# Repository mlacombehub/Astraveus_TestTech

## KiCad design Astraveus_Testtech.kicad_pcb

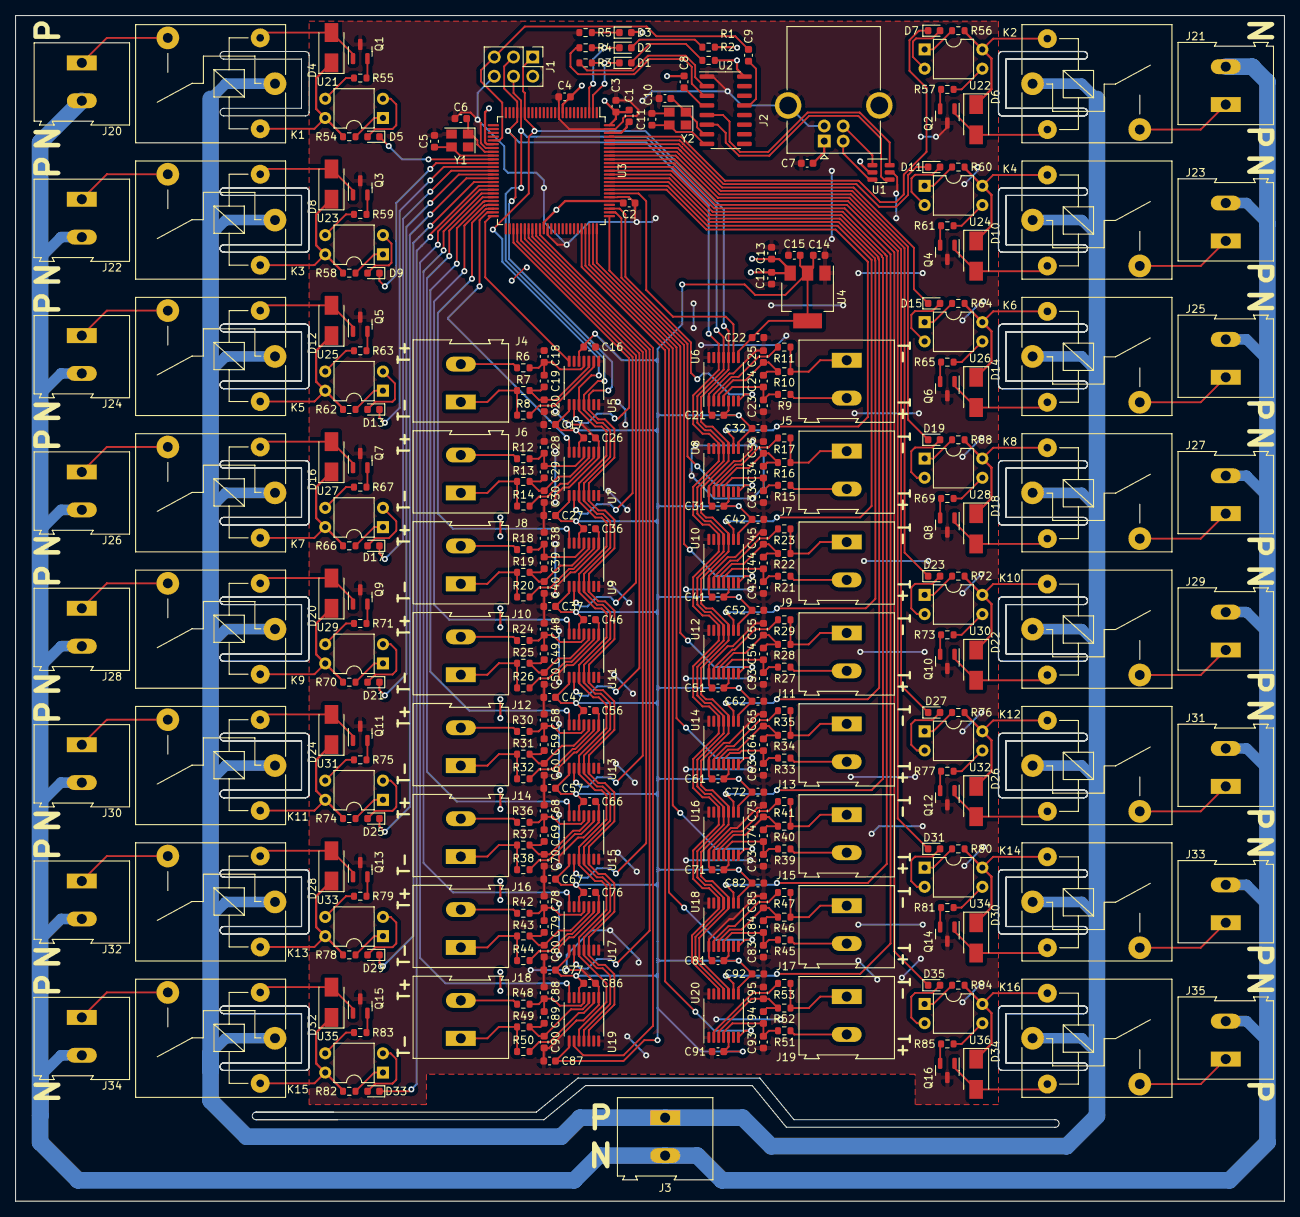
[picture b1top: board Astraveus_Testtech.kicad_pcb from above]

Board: 2 copper layers, 167.5 x 156.5 mm, 320 parts (0 on the bottom side), 251 nets.

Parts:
C1, C3, C4, C7, C8, C9, C16, C17, C19, C21, C22, C24, C26, C27, C29, C31, C32, C34, C36, C37, C39, C41, C42, C44, C46, C47, C49, C51, C52, C54, C56, C57, C59, C61, C62, C64, C66, C67, C69, C71, C72, C74, C76, C77, C79, C81, C82, C84, C86, C87, C89, C91, C92, C94: 100nF; C_0603_1608Metric
C2: 10uF; C_0603_1608Metric
C5, C6, C10, C11: 22pF; C_0603_1608Metric
C12, C15: 4.7uF; C_0603_1608Metric
C13, C14: 1uF; C_0603_1608Metric
C18, C20, C23, C25, C28, C30, C33, C35, C38, C40, C43, C45, C48, C50, C53, C55, C58, C60, C63, C65, C68, C70, C73, C75, C78, C80, C83, C85, C88, C90, C93, C95: 10nF; C_0603_1608Metric
D1, D2, D3, D5, D7, D9, D11, D13, D15, D17, D19, D21, D23, D25, D27, D29, D31, D33, D35: LED_Small; D_0603_1608Metric
D4, D6, D8, D10, D12, D14, D16, D18, D20, D22, D24, D26, D28, D30, D32, D34: 1N4007; D_SMA
J1: AVR-ISP-6; PinHeader_2x03_P2.54mm_Vertical
J2: USB_B; USB_B_OST_USB-B1HSxx_Horizontal
J3, J4, J5, J6, J7, J8, J9, J10, J11, J12, J13, J14, J15, J16, J17, J18, J19, J20, J21, J22, J23, J24, J25, J26, J27, J28, J29, J30, J31, J32, J33, J34, J35: Screw_Terminal_01x02; TerminalBlock_Altech_AK300-2_P5.00mm
K1, K2, K3, K4, K5, K6, K7, K8, K9, K10, K11, K12, K13, K14, K15, K16: SANYOU_SRD_Form_C; Relay_SPST_SANYOU_SRD_Series_Form_A
Q1, Q2, Q3, Q4, Q5, Q6, Q7, Q8, Q9, Q10, Q11, Q12, Q13, Q14, Q15, Q16: BC547; SOT-23
R1, R3: 10K; R_0603_1608Metric
R2, R4, R5: 1K; R_0603_1608Metric
R6, R7, R8, R9, R10, R11, R12, R13, R14, R15, R16, R17, R18, R19, R20, R21, R22, R23, R24, R25, R26, R27, R28, R29, R30, R31, R32, R33, R34, R35, R36, R37, R38, R39, R40, R41, R42, R43, R44, R45, R46, R47, R48, R49, R50, R51, R52, R53, R54, R55, R56, R57, R58, R59, R60, R61, R62, R63, R64, R65, R66, R67, R68, R69, R70, R71, R72, R73, R74, R75, R76, R77, R78, R79, R80, R81, R82, R83, R84, R85: 100; R_0603_1608Metric
U1: USBLC6-2SC6; SOT-23-6
U2: CH340G; SOIC-16_3.9x9.9mm_P1.27mm
U3: ATmega2560-16A; TQFP-100_14x14mm_P0.5mm
U4: AMS1117-3.3; SOT-223-3_TabPin2
U5, U6, U7, U8, U9, U10, U11, U12, U13, U14, U15, U16, U17, U18, U19, U20: MAX31856; TSSOP-14_4.4x5mm_P0.65mm
U21, U22, U23, U24, U25, U26, U27, U28, U29, U30, U31, U32, U33, U34, U35, U36: PC817; DIP-4_W7.62mm
Y1: 16MHz; Crystal_SMD_3225-4Pin_3.2x2.5mm
Y2: 12MHz; Crystal_SMD_3225-4Pin_3.2x2.5mm

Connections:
+3.3V: C14.1, C15.1, C16.2, C17.2, C21.2, C22.2, C26.2, C27.2, C31.2, C32.2, C36.2, C37.2, C41.2, C42.2, C46.2, C47.2, C51.2, C52.2, C56.2, C57.2, C61.2, C62.2, C66.2, C67.2, C71.2, C72.2, C76.2, C77.2, C81.2, C82.2, C86.2, C87.2, C91.2, C92.2, U4.2 (VO), U5.5 (AVDD), U5.8 (DVDD), U6.5 (AVDD), U6.8 (DVDD), U7.5 (AVDD), U7.8 (DVDD), U8.5 (AVDD), U8.8 (DVDD), U9.5 (AVDD), U9.8 (DVDD), U10.5 (AVDD), U10.8 (DVDD), U11.5 (AVDD), U11.8 (DVDD), U12.5 (AVDD), U12.8 (DVDD), U13.5 (AVDD), U13.8 (DVDD), U14.5 (AVDD), U14.8 (DVDD), U15.5 (AVDD), U15.8 (DVDD), U16.5 (AVDD), U16.8 (DVDD), U17.5 (AVDD), U17.8 (DVDD), U18.5 (AVDD), U18.8 (DVDD), U19.5 (AVDD), U19.8 (DVDD), U20.5 (AVDD), U20.8 (DVDD)
+5V: C1.1, C2.1, C3.1, C4.1, C7.1, C8.2, C12.1, C13.1, D3.2 (A), D4.1 (K), D6.1 (K), D8.1 (K), D10.1 (K), D12.1 (K), D14.1 (K), D16.1 (K), D18.1 (K), D20.1 (K), D22.1 (K), D24.1 (K), D26.1 (K), D28.1 (K), D30.1 (K), D32.1 (K), D34.1 (K), J1.2 (VCC), J2.1 (VBUS), K1.5, K2.5, K3.5, K4.5, K5.5, K6.5, K7.5, K8.5, K9.5, K10.5, K11.5, K12.5, K13.5, K14.5, K15.5, K16.5, R1.2, R2.2, R54.2, R56.2, R58.2, R60.2, R62.2, R64.2, R66.2, R68.2, R70.2, R72.2, R74.2, R76.2, R78.2, R80.2, R82.2, R84.2, U1.2 (GND), U2.16 (VCC), U3.10 (VCC), U3.31 (VCC), U3.61 (VCC), U3.80 (VCC), U3.100 (AVCC), U4.3 (VI), U21.4, U22.4, U23.4, U24.4, U25.4, U26.4, U27.4, U28.4, U29.4, U30.4, U31.4, U32.4, U33.4, U34.4, U35.4, U36.4
/AREF: C1.2, U3.98 (AREF)
/CH0: D5.1 (K), U3.35 (PL0)
/CH1: D7.1 (K), U3.97 (PF0)
/CH2: D9.1 (K), U3.36 (PL1)
/CH3: D11.1 (K), U3.96 (PF1)
/CH4: D13.1 (K), U3.37 (PL2)
/CH5: D15.1 (K), U3.95 (PF2)
/CH6: D17.1 (K), U3.38 (PL3)
/CH7: D19.1 (K), U3.94 (PF3)
/CH8: D21.1 (K), U3.39 (PL4)
/CH9: D23.1 (K), U3.93 (PF4)
/CH10: D25.1 (K), U3.40 (PL5)
/CH11: D27.1 (K), U3.92 (PF5)
/CH12: D29.1 (K), U3.41 (PL6)
/CH13: D31.1 (K), U3.91 (PF6)
/CH14: D33.1 (K), U3.42 (PL7)
/CH15: D35.1 (K), U3.90 (PF7)
/RESET: C9.2, J1.5 (~RST), U3.30 (~RESET)
/RX: D1.1 (K), R3.2, U3.2 (PE0)
/SPI0: J1.1 (MISO), U3.20 (PB1), U5.10 (SCK), U6.10 (SCK), U7.10 (SCK), U8.10 (SCK), U9.10 (SCK), U10.10 (SCK), U11.10 (SCK), U12.10 (SCK), U13.10 (SCK), U14.10 (SCK), U15.10 (SCK), U16.10 (SCK), U17.10 (SCK), U18.10 (SCK), U19.10 (SCK), U20.10 (SCK)
/SPI1: J1.4 (MOSI), U3.21 (PB2), U5.11 (SDO), U6.11 (SDO), U7.11 (SDO), U8.11 (SDO), U9.11 (SDO), U10.11 (SDO), U11.11 (SDO), U12.11 (SDO), U13.11 (SDO), U14.11 (SDO), U15.11 (SDO), U16.11 (SDO), U17.11 (SDO), U18.11 (SDO), U19.11 (SDO), U20.11 (SDO)
/SPI2: J1.3 (SCK), U3.22 (PB3), U5.12 (SDI), U6.12 (SDI), U7.12 (SDI), U8.12 (SDI), U9.12 (SDI), U10.12 (SDI), U11.12 (SDI), U12.12 (SDI), U13.12 (SDI), U14.12 (SDI), U15.12 (SDI), U16.12 (SDI), U17.12 (SDI), U18.12 (SDI), U19.12 (SDI), U20.12 (SDI)
/TX: D2.1 (K), R4.2, U3.3 (PE1)
/~CS0: U3.53 (PC0), U5.9 (~CS)
/~CS1: U3.82 (PK7), U6.9 (~CS)
/~CS2: U3.54 (PC1), U7.9 (~CS)
/~CS3: U3.83 (PK6), U8.9 (~CS)
/~CS4: U3.55 (PC2), U9.9 (~CS)
/~CS5: U3.84 (PK5), U10.9 (~CS)
/~CS6: U3.56 (PC3), U11.9 (~CS)
/~CS7: U3.85 (PK4), U12.9 (~CS)
/~CS8: U3.57 (PC4), U13.9 (~CS)
/~CS9: U3.86 (PK3), U14.9 (~CS)
/~CS10: U3.58 (PC5), U15.9 (~CS)
/~CS11: U3.87 (PK2), U16.9 (~CS)
/~CS12: U3.59 (PC6), U17.9 (~CS)
/~CS13: U3.88 (PK1), U18.9 (~CS)
/~CS14: U3.60 (PC7), U19.9 (~CS)
/~CS15: U3.89 (PK0), U20.9 (~CS)
/~DRDY0: U3.50 (PD7), U5.7 (~DRDY)
/~DRDY1: U3.78 (PA0), U6.7 (~DRDY)
/~DRDY2: U3.49 (PD6), U7.7 (~DRDY)
/~DRDY3: U3.77 (PA1), U8.7 (~DRDY)
/~DRDY4: U3.48 (PD5), U9.7 (~DRDY)
/~DRDY5: U3.76 (PA2), U10.7 (~DRDY)
/~DRDY6: U3.47 (PD4), U11.7 (~DRDY)
/~DRDY7: U3.75 (PA3), U12.7 (~DRDY)
/~DRDY8: U3.46 (PD3), U13.7 (~DRDY)
/~DRDY9: U3.74 (PA4), U14.7 (~DRDY)
/~DRDY10: U3.45 (PD2), U15.7 (~DRDY)
/~DRDY11: U3.73 (PA5), U16.7 (~DRDY)
/~DRDY12: U3.44 (PD1), U17.7 (~DRDY)
/~DRDY13: U3.72 (PA6), U18.7 (~DRDY)
/~DRDY14: U3.43 (PD0), U19.7 (~DRDY)
/~DRDY15: U3.71 (PA7), U20.7 (~DRDY)
GND: C2.2, C3.2, C4.2, C5.2, C6.2, C7.2, C10.2, C11.2, C12.2, C13.2, C14.2, C15.2, C16.1, C17.1, C18.1, C20.2, C21.1, C22.1, C23.1, C25.2, C26.1, C27.1, C28.1, C30.2, C31.1, C32.1, C33.1, C35.2, C36.1, C37.1, C38.1, C40.2, C41.1, C42.1, C43.1, C45.2, C46.1, C47.1, C48.1, C50.2, C51.1, C52.1, C53.1, C55.2, C56.1, C57.1, C58.1, C60.2, C61.1, C62.1, C63.1, C65.2, C66.1, C67.1, C68.1, C70.2, C71.1, C72.1, C73.1, C75.2, C76.1, C77.1, C78.1, C80.2, C81.1, C82.1, C83.1, C85.2, C86.1, C87.1, C88.1, C90.2, C91.1, C92.1, C93.1, C95.2, J1.6 (GND), J2.4 (GND), J2.5 (Shield), Q1.3 (E), Q2.3 (E), Q3.3 (E), Q4.3 (E), Q5.3 (E), Q6.3 (E), Q7.3 (E), Q8.3 (E), Q9.3 (E), Q10.3 (E), Q11.3 (E), Q12.3 (E), Q13.3 (E), Q14.3 (E), Q15.3 (E), Q16.3 (E), R5.1, U1.5 (VBUS), U2.1 (GND), U3.11 (GND), U3.32 (GND), U3.62 (GND), U3.81 (GND), U3.99 (GND), U4.1 (GND), U5.1 (AGND), U5.14 (DGND), U6.1 (AGND), U6.14 (DGND), U7.1 (AGND), U7.14 (DGND), U8.1 (AGND), U8.14 (DGND), U9.1 (AGND), U9.14 (DGND), U10.1 (AGND), U10.14 (DGND), U11.1 (AGND), U11.14 (DGND), U12.1 (AGND), U12.14 (DGND), U13.1 (AGND), U13.14 (DGND), U14.1 (AGND), U14.14 (DGND), U15.1 (AGND), U15.14 (DGND), U16.1 (AGND), U16.14 (DGND), U17.1 (AGND), U17.14 (DGND), U18.1 (AGND), U18.14 (DGND), U19.1 (AGND), U19.14 (DGND), U20.1 (AGND), U20.14 (DGND), Y1.2, Y2.2
GNDA: J3.2, J20.2, J21.2, J22.2, J23.2, J24.2, J25.2, J26.2, J27.2, J28.2, J29.2, J30.2, J31.2, J32.2, J33.2, J34.2, J35.2
unnamed: C5.1, U3.34 (XTAL1), Y1.3
unnamed: C6.1, U3.33 (XTAL2), Y1.1
unnamed: C8.1, U2.4 (V3)
unnamed: C9.1, U2.13 (~DTR)
unnamed: C10.1, U2.7 (XI), Y2.1
unnamed: C11.1, U2.8 (XO), Y2.3
unnamed: C18.2, C19.1, R6.2, U5.4 (T+)
unnamed: C19.2, C20.1, R7.2, U5.3 (T-)
unnamed: C23.2, C24.1, R9.2, U6.4 (T+)
unnamed: C24.2, C25.1, R10.2, U6.3 (T-)
unnamed: C28.2, C29.1, R12.2, U7.4 (T+)
unnamed: C29.2, C30.1, R13.2, U7.3 (T-)
unnamed: C33.2, C34.1, R15.2, U8.4 (T+)
unnamed: C34.2, C35.1, R16.2, U8.3 (T-)
unnamed: C38.2, C39.1, R18.2, U9.4 (T+)
unnamed: C39.2, C40.1, R19.2, U9.3 (T-)
unnamed: C43.2, C44.1, R21.2, U10.4 (T+)
unnamed: C44.2, C45.1, R22.2, U10.3 (T-)
unnamed: C48.2, C49.1, R24.2, U11.4 (T+)
unnamed: C49.2, C50.1, R25.2, U11.3 (T-)
unnamed: C53.2, C54.1, R27.2, U12.4 (T+)
unnamed: C54.2, C55.1, R28.2, U12.3 (T-)
unnamed: C58.2, C59.1, R30.2, U13.4 (T+)
unnamed: C59.2, C60.1, R31.2, U13.3 (T-)
unnamed: C63.2, C64.1, R33.2, U14.4 (T+)
unnamed: C64.2, C65.1, R34.2, U14.3 (T-)
unnamed: C68.2, C69.1, R36.2, U15.4 (T+)
unnamed: C69.2, C70.1, R37.2, U15.3 (T-)
unnamed: C73.2, C74.1, R39.2, U16.4 (T+)
unnamed: C74.2, C75.1, R40.2, U16.3 (T-)
unnamed: C78.2, C79.1, R42.2, U17.4 (T+)
unnamed: C79.2, C80.1, R43.2, U17.3 (T-)
unnamed: C83.2, C84.1, R45.2, U18.4 (T+)
unnamed: C84.2, C85.1, R46.2, U18.3 (T-)
unnamed: C88.2, C89.1, R48.2, U19.4 (T+)
unnamed: C89.2, C90.1, R49.2, U19.3 (T-)
unnamed: C93.2, C94.1, R51.2, U20.4 (T+)
unnamed: C94.2, C95.1, R52.2, U20.3 (T-)
unnamed: D1.2 (A), R1.1
unnamed: D2.2 (A), R2.1
unnamed: D3.1 (K), R5.2
unnamed: D4.2 (A), K1.2, Q1.1 (C)
unnamed: D5.2 (A), U21.2
unnamed: D6.2 (A), K2.2, Q2.1 (C)
unnamed: D7.2 (A), U22.2
unnamed: D8.2 (A), K3.2, Q3.1 (C)
unnamed: D9.2 (A), U23.2
unnamed: D10.2 (A), K4.2, Q4.1 (C)
unnamed: D11.2 (A), U24.2
unnamed: D12.2 (A), K5.2, Q5.1 (C)
unnamed: D13.2 (A), U25.2
unnamed: D14.2 (A), K6.2, Q6.1 (C)
unnamed: D15.2 (A), U26.2
unnamed: D16.2 (A), K7.2, Q7.1 (C)
unnamed: D17.2 (A), U27.2
unnamed: D18.2 (A), K8.2, Q8.1 (C)
unnamed: D19.2 (A), U28.2
unnamed: D20.2 (A), K9.2, Q9.1 (C)
unnamed: D21.2 (A), U29.2
unnamed: D22.2 (A), K10.2, Q10.1 (C)
unnamed: D23.2 (A), U30.2
unnamed: D24.2 (A), K11.2, Q11.1 (C)
unnamed: D25.2 (A), U31.2
unnamed: D26.2 (A), K12.2, Q12.1 (C)
unnamed: D27.2 (A), U32.2
unnamed: D28.2 (A), K13.2, Q13.1 (C)
unnamed: D29.2 (A), U33.2
unnamed: D30.2 (A), K14.2, Q14.1 (C)
unnamed: D31.2 (A), U34.2
unnamed: D32.2 (A), K15.2, Q15.1 (C)
unnamed: D33.2 (A), U35.2
unnamed: D34.2 (A), K16.2, Q16.1 (C)
unnamed: D35.2 (A), U36.2
unnamed: J2.2 (D-), U1.3 (I/O2)
unnamed: J2.3 (D+), U1.1 (I/O1)
unnamed: J4.1, R7.1, R8.1
unnamed: J4.2, R6.1
unnamed: J5.1, R10.1, R11.1
unnamed: J5.2, R9.1
unnamed: J6.1, R13.1, R14.1
unnamed: J6.2, R12.1
unnamed: J7.1, R16.1, R17.1
unnamed: J7.2, R15.1
unnamed: J8.1, R19.1, R20.1
unnamed: J8.2, R18.1
unnamed: J9.1, R22.1, R23.1
unnamed: J9.2, R21.1
unnamed: J10.1, R25.1, R26.1
unnamed: J10.2, R24.1
unnamed: J11.1, R28.1, R29.1
unnamed: J11.2, R27.1
unnamed: J12.1, R31.1, R32.1
unnamed: J12.2, R30.1
unnamed: J13.1, R34.1, R35.1
unnamed: J13.2, R33.1
unnamed: J14.1, R37.1, R38.1
unnamed: J14.2, R36.1
unnamed: J15.1, R40.1, R41.1
unnamed: J15.2, R39.1
unnamed: J16.1, R43.1, R44.1
unnamed: J16.2, R42.1
unnamed: J17.1, R46.1, R47.1
unnamed: J17.2, R45.1
unnamed: J18.1, R49.1, R50.1
unnamed: J18.2, R48.1
unnamed: J19.1, R52.1, R53.1
unnamed: J19.2, R51.1
unnamed: J20.1, K1.3
unnamed: J21.1, K2.3
unnamed: J22.1, K3.3
unnamed: J23.1, K4.3
unnamed: J24.1, K5.3
unnamed: J25.1, K6.3
unnamed: J26.1, K7.3
unnamed: J27.1, K8.3
unnamed: J28.1, K9.3
unnamed: J29.1, K10.3
unnamed: J30.1, K11.3
unnamed: J31.1, K12.3
unnamed: J32.1, K13.3
unnamed: J33.1, K14.3
unnamed: J34.1, K15.3
unnamed: J35.1, K16.3
unnamed: Q1.2 (B), R55.1
unnamed: Q2.2 (B), R57.1
unnamed: Q3.2 (B), R59.1
unnamed: Q4.2 (B), R61.1
unnamed: Q5.2 (B), R63.1
unnamed: Q6.2 (B), R65.1
unnamed: Q7.2 (B), R67.1
unnamed: Q8.2 (B), R69.1
unnamed: Q9.2 (B), R71.1
unnamed: Q10.2 (B), R73.1
unnamed: Q11.2 (B), R75.1
unnamed: Q12.2 (B), R77.1
unnamed: Q13.2 (B), R79.1
unnamed: Q14.2 (B), R81.1
unnamed: Q15.2 (B), R83.1
unnamed: Q16.2 (B), R85.1
unnamed: R3.1, U2.2 (TXD)
unnamed: R4.1, U2.3 (RXD)
unnamed: R8.2, U5.2 (BIAS)
unnamed: R11.2, U6.2 (BIAS)
unnamed: R14.2, U7.2 (BIAS)
unnamed: R17.2, U8.2 (BIAS)
unnamed: R20.2, U9.2 (BIAS)
unnamed: R23.2, U10.2 (BIAS)
unnamed: R26.2, U11.2 (BIAS)
unnamed: R29.2, U12.2 (BIAS)
unnamed: R32.2, U13.2 (BIAS)
unnamed: R35.2, U14.2 (BIAS)
unnamed: R38.2, U15.2 (BIAS)
unnamed: R41.2, U16.2 (BIAS)
unnamed: R44.2, U17.2 (BIAS)
unnamed: R47.2, U18.2 (BIAS)
unnamed: R50.2, U19.2 (BIAS)
unnamed: R53.2, U20.2 (BIAS)
unnamed: R54.1, U21.1
unnamed: R55.2, U21.3
unnamed: R56.1, U22.1
unnamed: R57.2, U22.3
unnamed: R58.1, U23.1
unnamed: R59.2, U23.3
unnamed: R60.1, U24.1
unnamed: R61.2, U24.3
unnamed: R62.1, U25.1
unnamed: R63.2, U25.3
unnamed: R64.1, U26.1
unnamed: R65.2, U26.3
unnamed: R66.1, U27.1
unnamed: R67.2, U27.3
unnamed: R68.1, U28.1
unnamed: R69.2, U28.3
unnamed: R70.1, U29.1
unnamed: R71.2, U29.3
unnamed: R72.1, U30.1
unnamed: R73.2, U30.3
unnamed: R74.1, U31.1
unnamed: R75.2, U31.3
unnamed: R76.1, U32.1
unnamed: R77.2, U32.3
unnamed: R78.1, U33.1
unnamed: R79.2, U33.3
unnamed: R80.1, U34.1
unnamed: R81.2, U34.3
unnamed: R82.1, U35.1
unnamed: R83.2, U35.3
unnamed: R84.1, U36.1
unnamed: R85.2, U36.3
unnamed: U1.4 (I/O2), U2.6 (UD-)
unnamed: U1.6 (I/O1), U2.5 (UD+)
VAC: J3.1, K1.1, K2.1, K3.1, K4.1, K5.1, K6.1, K7.1, K8.1, K9.1, K10.1, K11.1, K12.1, K13.1, K14.1, K15.1, K16.1

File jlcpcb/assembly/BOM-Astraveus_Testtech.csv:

Comment,Designator,Footprint,LCSC
USB_B,J2,USB_B_OST_USB-B1HSxx_Horizontal,C114097
MAX31856,"U10,U11,U12,U13,U14,U15,U16,U17,U18,U19,U20,U5,U6,U7,U8,U9",TSSOP-14_4.4x5mm_P0.65mm,C116632
100,"R10,R11,R12,R13,R14,R15,R16,R17,R18,R19,R20,R21,R22,R23,R24,R25,R26,R27,R28,R29,R30,R31,R32,R33,R34,R35,R36,R37,R38,R39,R40,R41,R42,R43,R44,R45,R46,R47,R48,R49,R50,R51,R52,R53,R54,R55,R56,R57,R58,R59,R6,R60,R61,R62,R63,R64,R65,R66,R67,R68,R69,R7,R70,R71,R72,R73,R74,R75,R76,R77,R78,R79,R8,R80,R81,R82,R83,R84,R85,R9",R_0603_1608Metric,C1203
LED_Small,"D1,D11,D13,D15,D17,D19,D2,D21,D23,D25,D27,D29,D31,D33,D35,D5,D7,D9",D_0603_1608Metric,C12065
1K,"R2,R4,R5",R_0603_1608Metric,C13015
CH340G,U2,SOIC-16_3.9x9.9mm_P1.27mm,C14267
10K,"R1,R3",R_0603_1608Metric,C15401
10nF,"C18,C20,C23,C25,C28,C30,C33,C35,C38,C40,C43,C45,C48,C50,C53,C55,C58,C60,C63,C65,C68,C70,C73,C75,C78,C80,C83,C85,C88,C90,C93,C95",C_0603_1608Metric,C1589
100nF,"C1,C16,C17,C19,C21,C22,C24,C26,C27,C29,C3,C31,C32,C34,C36,C37,C39,C4,C41,C42,C44,C46,C47,C49,C51,C52,C54,C56,C57,C59,C61,C62,C64,C66,C67,C69,C7,C71,C72,C74,C76,C77,C79,C8,C81,C82,C84,C86,C87,C89,C9,C91,C92,C94",C_0603_1608Metric,C1590
1uF,"C13,C14",C_0603_1608Metric,C1592
22pF,"C10,C11,C5,C6",C_0603_1608Metric,C1653
10uF,C2,C_0603_1608Metric,C1691
4.7uF,"C12,C15",C_0603_1608Metric,C1705
ATmega2560-16A,U3,TQFP-100_14x14mm_P0.5mm,C22460
1N4007,"D10,D12,D14,D16,D18,D20,D22,D24,D26,D28,D30,D32,D34,D4,D6,D8",D_SMA,C2909831
BC547,"Q1,Q10,Q11,Q12,Q13,Q14,Q15,Q16,Q2,Q3,Q4,Q5,Q6,Q7,Q8,Q9",SOT-23,C2922743
PC817,"U21,U22,U23,U24,U25,U26,U27,U28,U29,U30,U31,U32,U33,U34,U35,U36",DIP-4_W7.62mm,C5351
AMS1117-3.3,U4,SOT-223-3_TabPin2,C6186
AVR-ISP-6,J1,PinHeader_2x03_P2.54mm_Vertical,C65114
SANYOU_SRD_Form_C,"K1,K10,K11,K12,K13,K14,K15,K16,K2,K3,K4,K5,K6,K7,K8,K9",Relay_SPST_SANYOU_SRD_Series_Form_A,C688862
LED_Small,D3,D_0603_1608Metric,C72044
USBLC6-2SC6,U1,SOT-23-6,C7519
Screw_Terminal_01x02,"J10,J11,J12,J13,J14,J15,J16,J17,J18,J19,J20,J21,J22,J23,J24,J25,J26,J27,J28,J29,J3,J30,J31,J32,J33,J34,J35,J4,J5,J6,J7,J8,J9",TerminalBlock_Altech_AK300-2_P5.00mm,C8465
12MHz,Y2,Crystal_SMD_3225-4Pin_3.2x2.5mm,C90900
16MHz,Y1,Crystal_SMD_3225-4Pin_3.2x2.5mm,C90906

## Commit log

2023-01-13 adding components for fab
